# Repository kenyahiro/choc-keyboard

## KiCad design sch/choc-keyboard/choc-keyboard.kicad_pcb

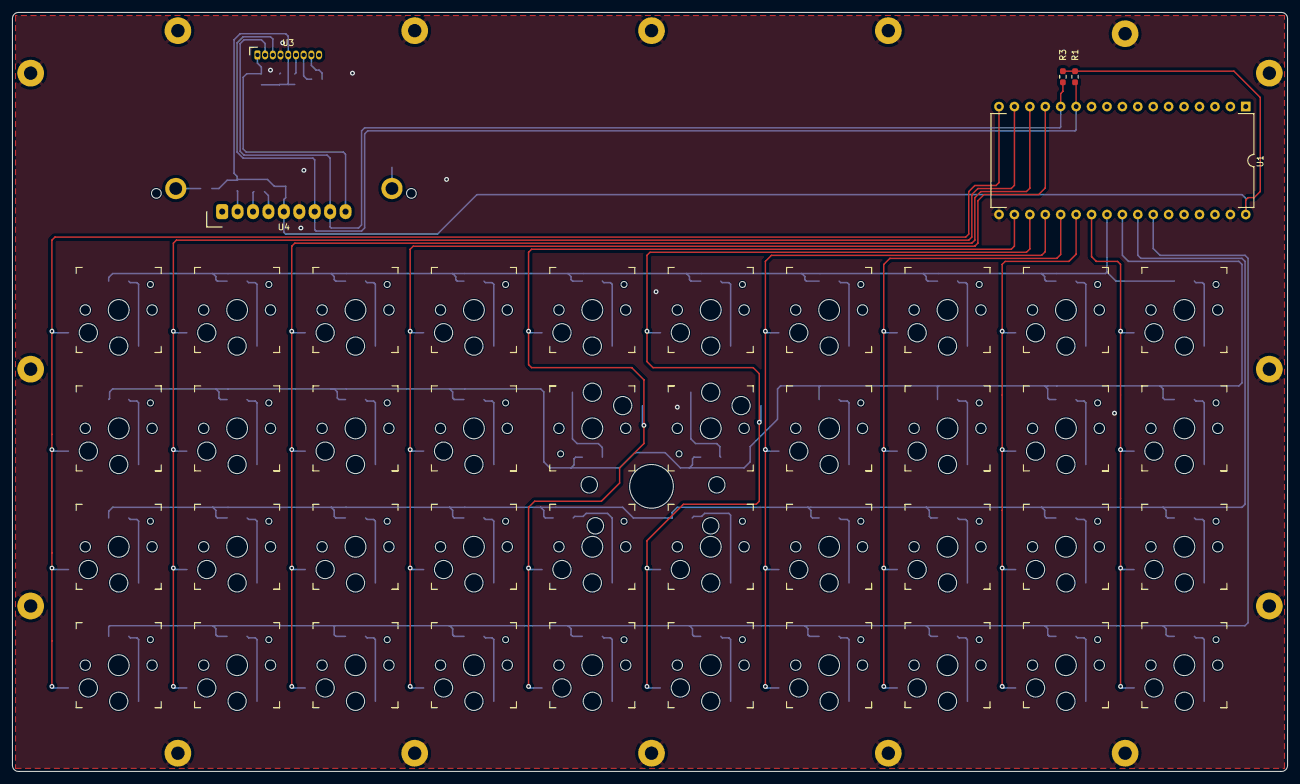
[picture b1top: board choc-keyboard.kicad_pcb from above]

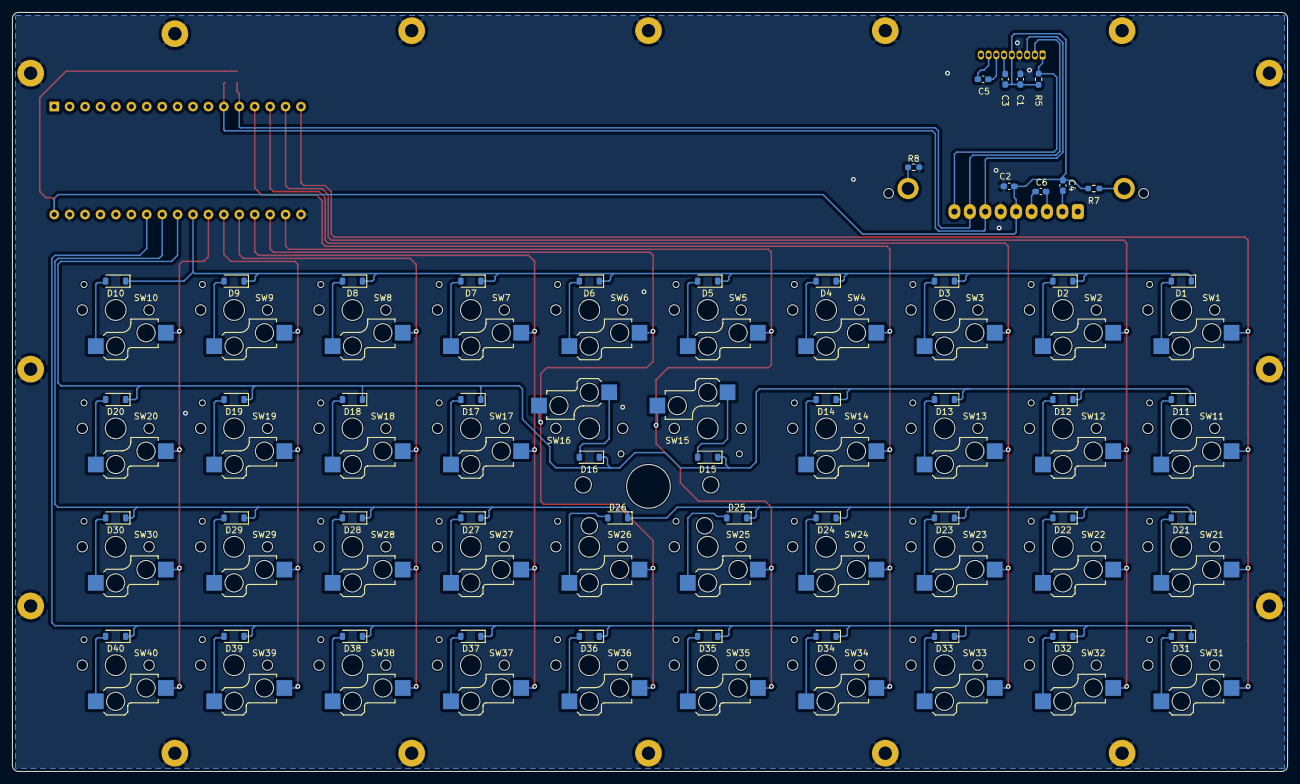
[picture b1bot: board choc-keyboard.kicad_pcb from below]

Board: 2 copper layers, 210.0 x 125.0 mm, 111 parts (49 on the bottom side), 67 nets.

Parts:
C1, C2, C3, C4, C5, C6: 1u; C_0603_1608Metric_Pad1.08x0.95mm_HandSolder
D1, D2, D3, D4, D5, D6, D7, D8, D9, D10, D11, D12, D13, D14, D15, D16, D17, D18, D19, D20, D21, D22, D23, D24, D25, D26, D27, D28, D29, D30, D31, D32, D33, D34, D35, D36, D37, D38, D39, D40: 1N4148W; D_SOD-123
H1, H2, H3, H4, H5, H6, H7, H8, H9, H10, H11, H12, H13, H14, H15, H16: MountingHole_Pad; MountingHole_2.2mm_M2_Pad
R1, R3, R5: 10k; R_0603_1608Metric_Pad0.98x0.95mm_HandSolder
R7: 1k; R_0603_1608Metric_Pad0.98x0.95mm_HandSolder
R8: 0; R_0603_1608Metric_Pad0.98x0.95mm_HandSolder
SW1, SW2, SW3, SW4, SW5, SW6, SW7, SW8, SW9, SW10, SW11, SW12, SW13, SW14, SW15, SW16, SW17, SW18, SW19, SW20, SW21, SW22, SW23, SW24, SW25, SW26, SW27, SW28, SW29, SW30, SW31, SW32, SW33, SW34, SW35, SW36, SW37, SW38, SW39, SW40: SW_Push; Kailh_socket_PG1350
U1: AE-RP2040
U2: trackpoint_t400
U3: AQM1602XA-RN-GBW
U4: AQM1602Y-NLW-FBW

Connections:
+3.3V: C1.1, C2.1, C3.1, C4.1, R1.1, R3.1, R5.1, R7.2, U1.34 (+3.3V), U3.5 (VDD), U4.5 (VDD)
/COL0: SW1.2, SW11.2, SW21.2, SW31.2, U1.17 (GPIO15)
/COL1: SW2.2, SW12.2, SW22.2, SW32.2, U1.16 (GPIO14)
/COL2: SW3.2, SW13.2, SW23.2, SW33.2, U1.15 (GPIO13)
/COL3: SW4.2, SW14.2, SW24.2, SW34.2, U1.14 (GPIO12)
/COL4: SW5.2, SW15.2, SW25.2, SW35.2, U1.19 (GPIO16)
/COL5: SW6.2, SW16.2, SW26.2, SW36.2, U1.20 (GPIO17)
/COL6: SW7.2, SW17.2, SW27.2, SW37.2, U1.21 (GPIO18)
/COL7: SW8.2, SW18.2, SW28.2, SW38.2, U1.22 (GPIO19)
/COL8: SW9.2, SW19.2, SW29.2, SW39.2, U1.23 (GPIO20)
/COL9: SW10.2, SW20.2, SW30.2, SW40.2, U1.24 (GPIO21)
/LCD_I2C_SCL: R3.2, U1.13 (GPIO11), U3.2 (SCL), U4.8 (SCL)
/LCD_I2C_SDA: R1.2, U1.12 (GPIO10), U3.3 (SDA), U4.7 (SDA)
/ROW0: D1.1 (K), D2.1 (K), D3.1 (K), D4.1 (K), D5.1 (K), D6.1 (K), D7.1 (K), D8.1 (K), D9.1 (K), D10.1 (K), U1.25 (GPIO22)
/ROW1: D11.1 (K), D12.1 (K), D13.1 (K), D14.1 (K), D15.1 (K), D16.1 (K), D17.1 (K), D18.1 (K), D19.1 (K), D20.1 (K), U1.26 (GPIO23)
/ROW2: D21.1 (K), D22.1 (K), D23.1 (K), D24.1 (K), D25.1 (K), D26.1 (K), D27.1 (K), D28.1 (K), D29.1 (K), D30.1 (K), U1.27 (GPIO24)
/ROW3: D31.1 (K), D32.1 (K), D33.1 (K), D34.1 (K), D35.1 (K), D36.1 (K), D37.1 (K), D38.1 (K), D39.1 (K), D40.1 (K), U1.28 (GPIO25)
GND: C1.2, C2.2, H1.1, H2.1, H3.1, H4.1, H5.1, H6.1, H7.1, H8.1, H9.1, H10.1, H11.1, H12.1, H13.1, H14.1, H15.1, H16.1, R8.2, U1.18 (GND), U1.33 (GND), U3.4 (VSS), U4.6 (VSS)
unnamed: D1.2 (A), SW1.1
unnamed: D2.2 (A), SW2.1
unnamed: D3.2 (A), SW3.1
unnamed: D4.2 (A), SW4.1
unnamed: D5.2 (A), SW5.1
unnamed: D6.2 (A), SW6.1
unnamed: D7.2 (A), SW7.1
unnamed: D8.2 (A), SW8.1
unnamed: D9.2 (A), SW9.1
unnamed: D10.2 (A), SW10.1
unnamed: D11.2 (A), SW11.1
unnamed: D12.2 (A), SW12.1
unnamed: D13.2 (A), SW13.1
unnamed: D14.2 (A), SW14.1
unnamed: D15.2 (A), SW15.1
unnamed: D16.2 (A), SW16.1
unnamed: D17.2 (A), SW17.1
unnamed: D18.2 (A), SW18.1
unnamed: D19.2 (A), SW19.1
unnamed: D20.2 (A), SW20.1
unnamed: D21.2 (A), SW21.1
unnamed: D22.2 (A), SW22.1
unnamed: D23.2 (A), SW23.1
unnamed: D24.2 (A), SW24.1
unnamed: D25.2 (A), SW25.1
unnamed: D26.2 (A), SW26.1
unnamed: D27.2 (A), SW27.1
unnamed: D28.2 (A), SW28.1
unnamed: D29.2 (A), SW29.1
unnamed: D30.2 (A), SW30.1
unnamed: D31.2 (A), SW31.1
unnamed: D32.2 (A), SW32.1
unnamed: D33.2 (A), SW33.1
unnamed: D34.2 (A), SW34.1
unnamed: D35.2 (A), SW35.1
unnamed: D36.2 (A), SW36.1
unnamed: D37.2 (A), SW37.1
unnamed: D38.2 (A), SW38.1
unnamed: D39.2 (A), SW39.1
unnamed: D40.2 (A), SW40.1
unnamed: C5.2, U3.8 (CAP1N)
unnamed: C5.1, U3.7 (CAP1P)
unnamed: R5.2, U3.1 (RES_N), U4.9 (RES_N)
unnamed: C3.2, U3.6 (VOUT)
unnamed: C6.2, U4.3 (CAP1N)
unnamed: C6.1, U4.4 (CAP1P)
unnamed: R7.1, U4.10 (LED_A)
unnamed: R8.1, U4.11 (LED_K)
unnamed: C4.2, U4.2 (VOUT)

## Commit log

2023-08-14 ざっくり配置して配線しました。
2023-08-15 トラックポイント取り付け用の穴位置の検討。
2023-08-15 配線しながらマイコンのピン配を検討中。
2023-08-15 ネジ穴のぶん基板を大きくしました。
2023-08-15 キャラクタLCDを追加。
